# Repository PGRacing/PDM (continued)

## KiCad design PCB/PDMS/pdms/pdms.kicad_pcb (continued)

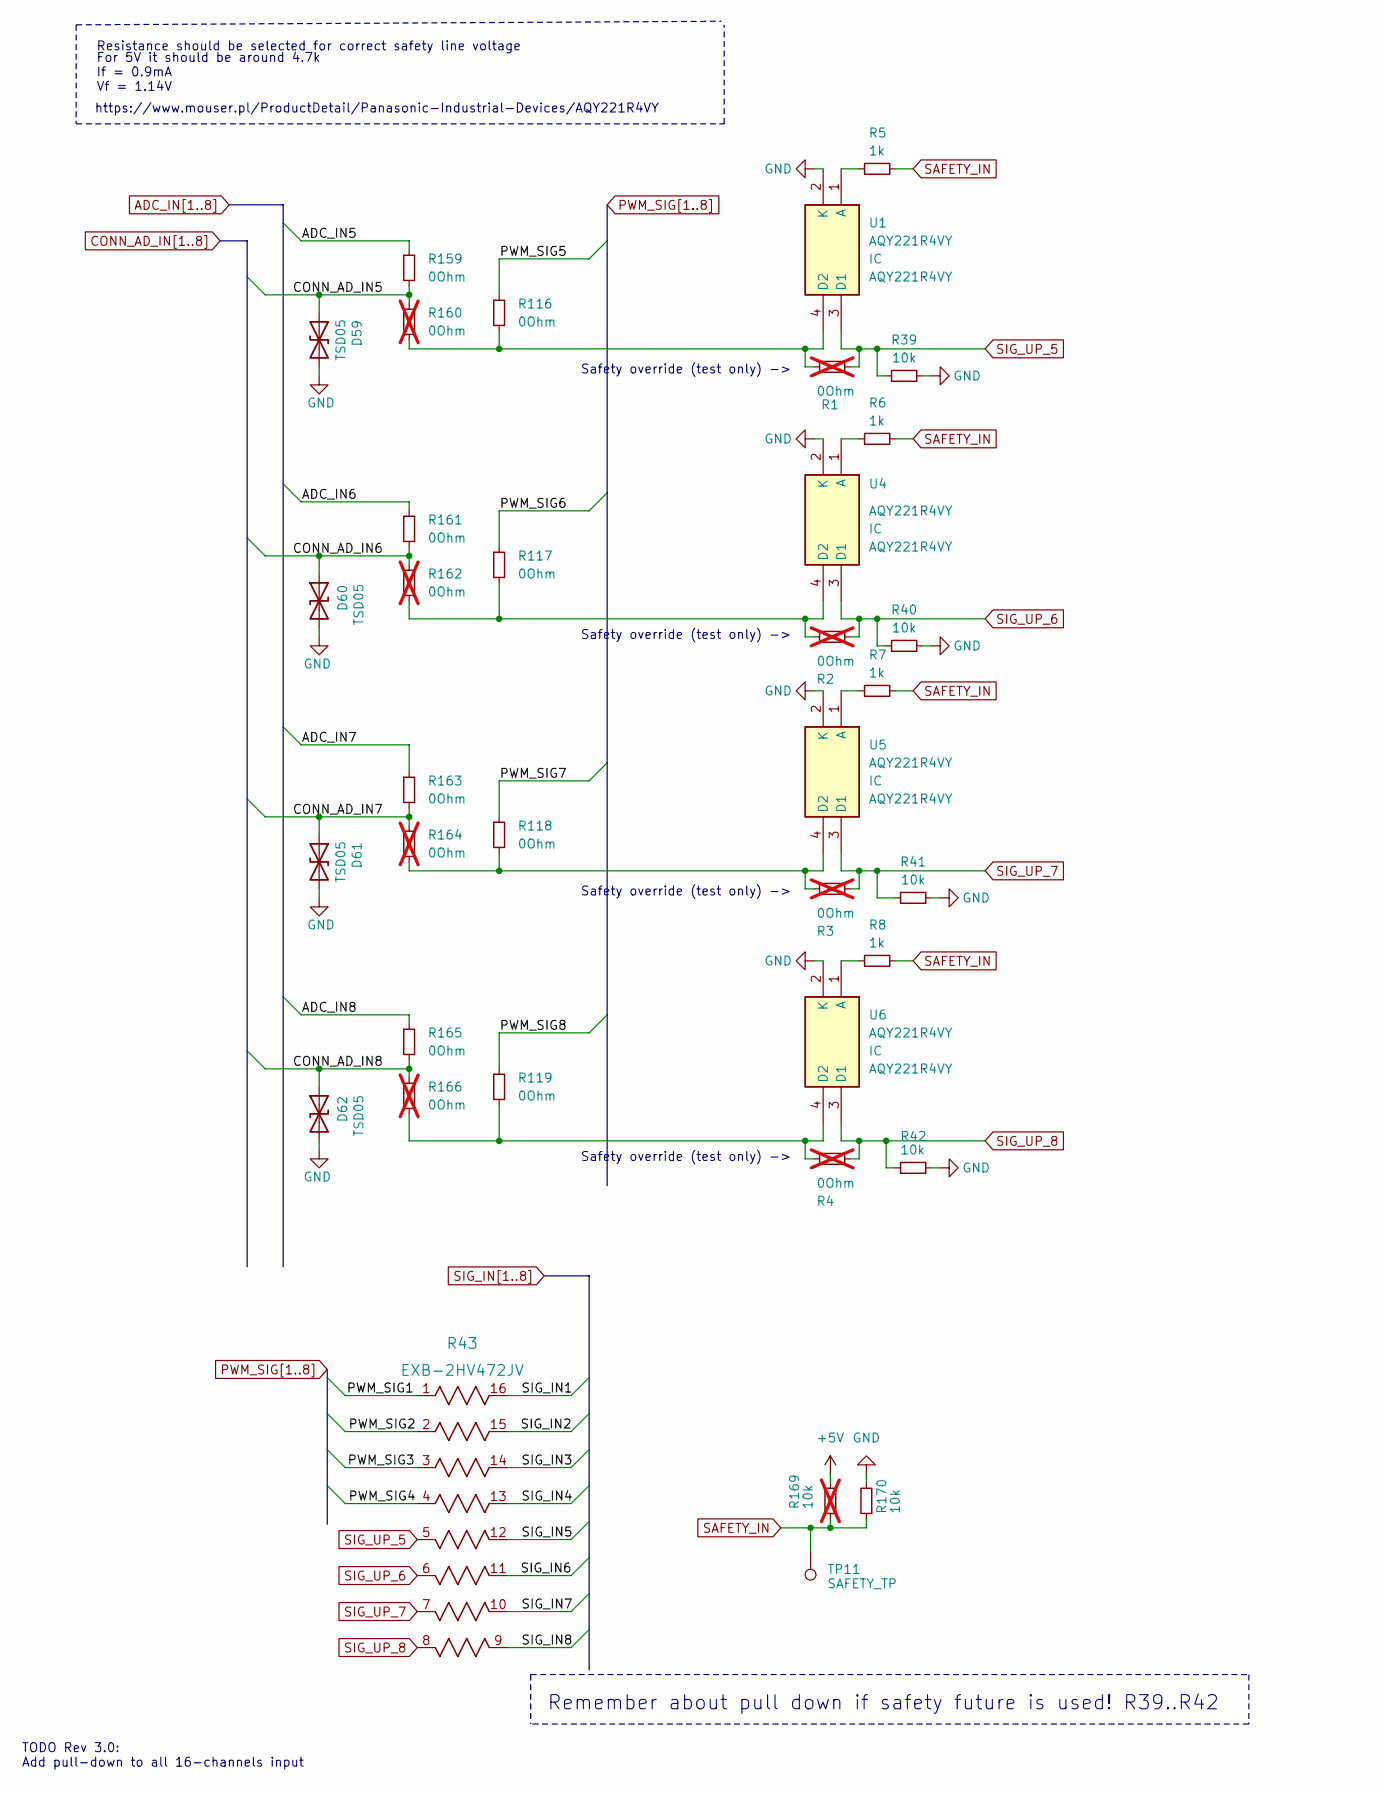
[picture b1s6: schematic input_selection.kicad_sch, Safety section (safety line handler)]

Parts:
D59, D60, D61, D62: TSD05; D_SOD-323
R1, R2, R3, R4, R160, R162, R164, R166: 0Ohm; R_0402_1005Metric; not fitted
R5, R6, R7, R8: 1k; R_0402_1005Metric
R39, R40, R41, R42, R170: 10k; R_0402_1005Metric
R43: EXB-2HV472JV; RES_EXB2HV
R116, R117, R118, R119, R159, R161, R163, R165: 0Ohm; R_0402_1005Metric
R169: 10k; R_0402_1005Metric; not fitted
TP11: SAFETY_TP; TestPoint_Pad_D2.0mm
U1, U4, U5, U6: AQY221R4VY; SOTFL127P485X190-4N; Manufacturer_Part_Number AQY221R4VY; Mouser Part Number 769-AQY221R4VY

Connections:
+5V: R169.2; also elsewhere on the board
ADC_IN5: R159.1; also elsewhere on the board
ADC_IN6: R161.1; also elsewhere on the board
ADC_IN7: R163.1; also elsewhere on the board
ADC_IN8: R165.1; also elsewhere on the board
CONN_AD_IN5: D59.1 (A1), R159.2, R160.1; also elsewhere on the board
CONN_AD_IN6: D60.1 (A1), R161.2, R162.1; also elsewhere on the board
CONN_AD_IN7: D61.1 (A1), R163.2, R164.1; also elsewhere on the board
CONN_AD_IN8: D62.1 (A1), R165.2, R166.1; also elsewhere on the board
unnamed: R5.1, U1.1 (A)
unnamed: R6.1, U4.1 (A)
unnamed: R7.1, U5.1 (A)
unnamed: R3.2, R118.2, R164.2, U5.4 (D2)
unnamed: R8.1, U6.1 (A)
unnamed: R4.2, R119.2, R166.2, U6.4 (D2)
PWM_SIG1: R43.1; also elsewhere on the board
PWM_SIG2: R43.2; also elsewhere on the board
PWM_SIG3: R43.3; also elsewhere on the board
PWM_SIG4: R43.4; also elsewhere on the board
PWM_SIG5: R116.1; also elsewhere on the board
PWM_SIG6: R117.1; also elsewhere on the board
PWM_SIG7: R118.1; also elsewhere on the board
PWM_SIG8: R119.1; also elsewhere on the board
SAFETY_IN: R5.2, R6.2, R7.2, R8.2, R169.1, R170.1, TP11.1; also elsewhere on the board
SIG_IN1: R43.16; also elsewhere on the board
SIG_IN2: R43.15; also elsewhere on the board
SIG_IN3: R43.14; also elsewhere on the board
SIG_IN4: R43.13; also elsewhere on the board
SIG_IN5: R43.12; also elsewhere on the board
SIG_IN6: R43.11; also elsewhere on the board
SIG_IN7: R43.10; also elsewhere on the board
SIG_IN8: R43.9; also elsewhere on the board
SIG_UP_7: R3.1, R41.1, R43.7, U5.3 (D1)
SIG_UP_8: R4.1, R42.1, R43.8, U6.3 (D1)

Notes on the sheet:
For 5V it should be around 4.7k If = 0.9mA Vf = 1.14V
Remember about pull down if safety future is used! R39..R42
Safety override (test only) ->
Resistance should be selected for correct safety line voltage
https://www.mouser.pl/ProductDetail/Panasonic-Industrial-Devices/AQY221R4VY
TODO Rev 3.0: Add pull-down to all 16-channels input

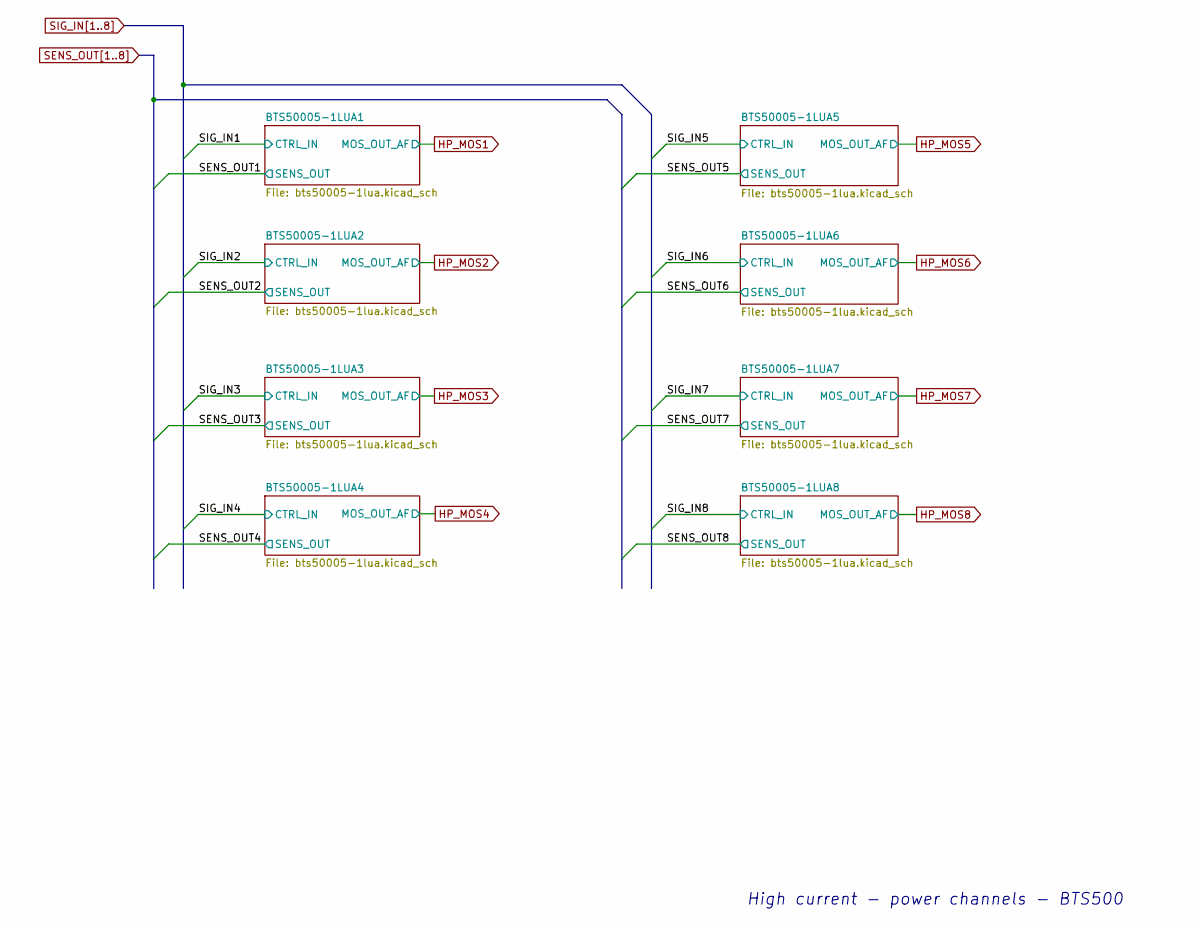
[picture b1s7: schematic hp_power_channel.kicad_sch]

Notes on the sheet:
High current - power channels - BTS500

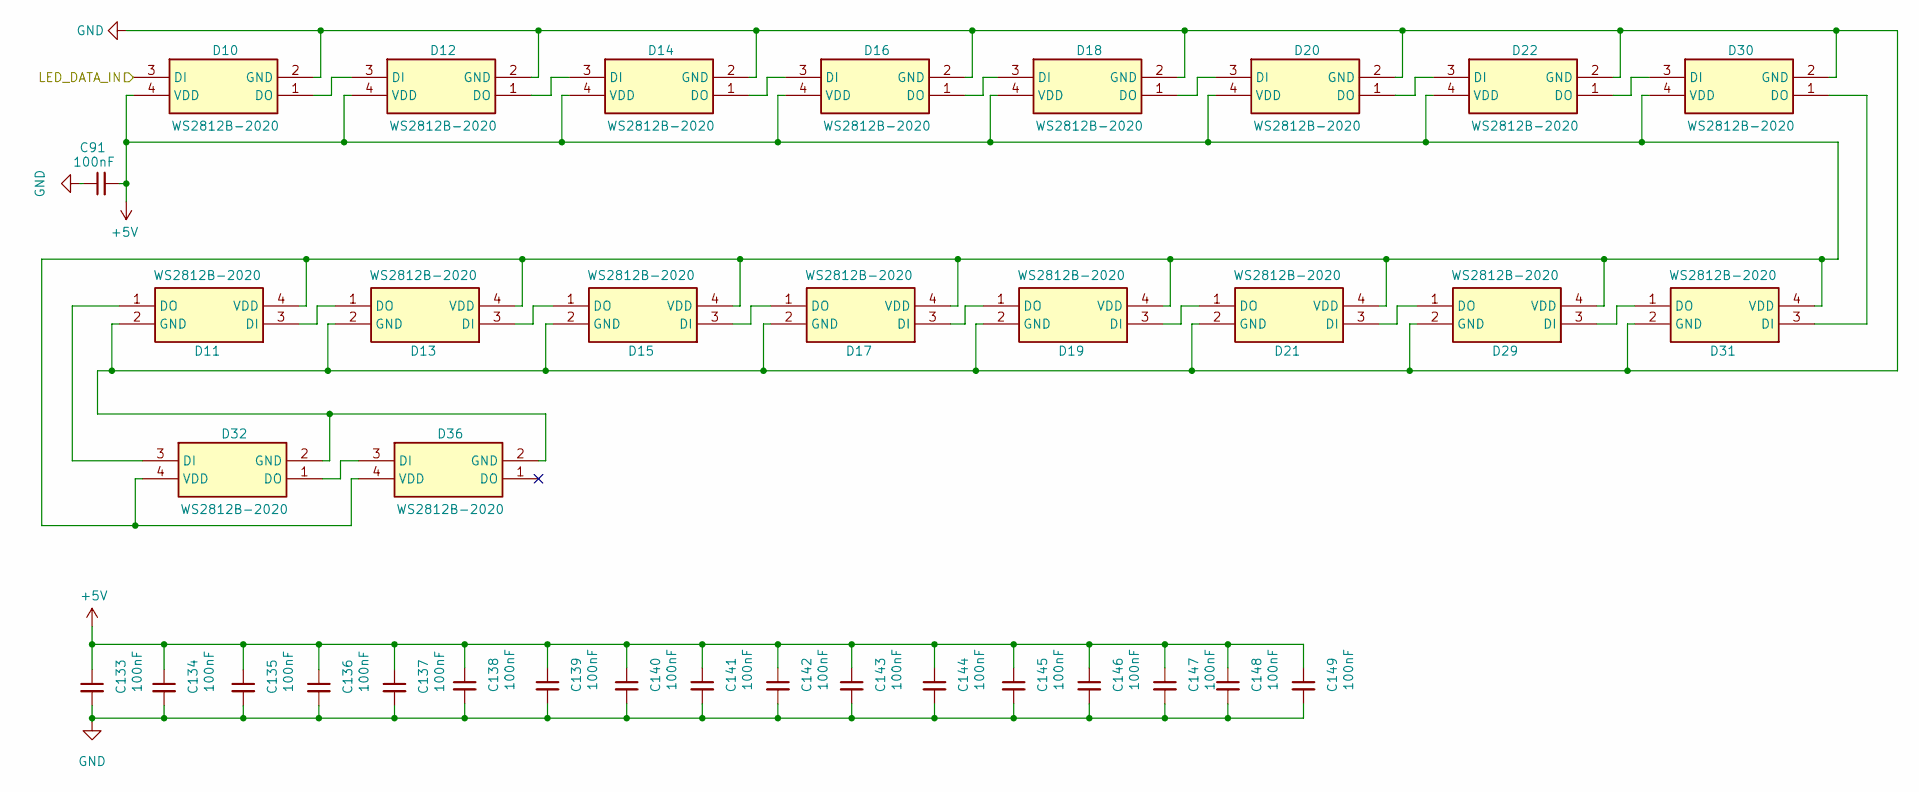
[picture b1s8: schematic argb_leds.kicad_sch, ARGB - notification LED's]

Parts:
C91, C133, C134, C135, C136, C137, C138, C139, C140, C141, C142, C143, C144, C145, C146, C147, C148, C149: 100nF; R_0402_1005Metric
D10, D11, D12, D13, D14, D15, D16, D17, D18, D19, D20, D21, D22, D29, D30, D31, D32, D36: WS2812B-2020; WS2812B2020; Manufacturer_Part_Number WS2812B-2020

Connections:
+5V: C91.2, C133.1, C134.1, C135.1, C136.1, C137.1, C138.1, C139.1, C140.1, C141.1, C142.1, C143.1, C144.1, C145.1, C146.1, C147.1, C148.1, C149.1, D10.4 (VDD), D11.4 (VDD), D12.4 (VDD), D13.4 (VDD), D14.4 (VDD), D15.4 (VDD), D16.4 (VDD), D17.4 (VDD), D18.4 (VDD), D19.4 (VDD), D20.4 (VDD), D21.4 (VDD), D22.4 (VDD), D29.4 (VDD), D30.4 (VDD), D31.4 (VDD), D32.4 (VDD), D36.4 (VDD); also elsewhere on the board
/ARGB_LEDS/LED_DATA_IN: D10.3 (DI); also elsewhere on the board
unnamed: D10.1 (DO), D12.3 (DI)
unnamed: D11.3 (DI), D13.1 (DO)
unnamed: D11.1 (DO), D32.3 (DI)
unnamed: D12.1 (DO), D14.3 (DI)
unnamed: D13.3 (DI), D15.1 (DO)
unnamed: D14.1 (DO), D16.3 (DI)
unnamed: D15.3 (DI), D17.1 (DO)
unnamed: D16.1 (DO), D18.3 (DI)
unnamed: D17.3 (DI), D19.1 (DO)
unnamed: D18.1 (DO), D20.3 (DI)
unnamed: D19.3 (DI), D21.1 (DO)
unnamed: D20.1 (DO), D22.3 (DI)
unnamed: D21.3 (DI), D29.1 (DO)
unnamed: D22.1 (DO), D30.3 (DI)
unnamed: D29.3 (DI), D31.1 (DO)
unnamed: D30.1 (DO), D31.3 (DI)
unnamed: D32.1 (DO), D36.3 (DI)

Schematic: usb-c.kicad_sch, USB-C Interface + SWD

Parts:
J6: 2305018-2; TE_2305018-2; not fitted
R173, R175: 1k5; R_0402_1005Metric; not fitted
R174, R176: 22; R_0402_1005Metric; not fitted
R177, R178: 5.1k; R_0402_1005Metric; not fitted
R179, R180: 0; R_0402_1005Metric; not fitted
U12: USBLC6-2SC6; SOT-23-6; not fitted

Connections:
+5V: U12.5 (VBUS); also elsewhere on the board
/USB-C/USB_D+: U12.4 (I/O2); also elsewhere on the board
/USB-C/USB_D-: U12.6 (I/O1); also elsewhere on the board
unnamed: J6.A5 (CC1), R177.1
unnamed: J6.B5 (CC2), R178.1
unnamed: R174.1, U12.1 (I/O1)
unnamed: R176.2, U12.3 (I/O2)
SWCLK: R180.1; also elsewhere on the board
SWDIO: R179.1; also elsewhere on the board
USBC_SWCLK: J6.A10 (RX2_N), J6.B10 (RX1_N), R180.2
USBC_SWDIO: J6.A11 (RX2_P), J6.B11 (RX1_P), R179.2
USB_CONN_D+: J6.A6 (DA_P), J6.B6 (DB_P), R175.1, R176.1
USB_CONN_D-: J6.A7 (DA_N), J6.B7 (DB_N), R173.1, R174.2

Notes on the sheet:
USB-C Legacy mode + Optional STLINK
USB-C Interface + SWD

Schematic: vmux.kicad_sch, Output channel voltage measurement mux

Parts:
C2, C112: 100nF; C_0402_1005Metric
C107: 47nF; C_0402_1005Metric
C1901, C1902, C1903, C1904, C1905, C1906, C1907, C1908: 4.7uF; C_0402_1005Metric
D38: BAT54SW; SOT-323_SC-70
D67: SZMM5Z3V9; D_SOD-523
IC2: 74HC4067PW-Q100J; SOP65P640X110-24N; Manufacturer_Part_Number 74HC4067PW-Q100J; Mouser Part Number 771-74HC4067PW-Q100J
R10, R13, R14, R17, R18, R33, R34, R37, R45, R48, R49, R52, R53, R88, R89, R92: 2.3k; R_0402_1005Metric
R11, R12, R15, R16, R19, R32, R35, R36, R46, R47, R50, R51, R65, R87, R90, R91: 10k; R_0402_1005Metric
R122: 1k; R_0402_1005Metric
U13: MCP6001-OT; SOT-23-5

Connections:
/VMUX/HP_MOS_DIV1: C1908.2, IC2.9 (Y0), R35.1, R37.2
/VMUX/HP_MOS_DIV2: C1907.2, IC2.8 (Y1), R19.1, R33.2
/VMUX/HP_MOS_DIV3: C1906.2, IC2.7 (Y2), R15.1, R17.2
/VMUX/HP_MOS_DIV4: C1905.2, IC2.6 (Y3), R11.1, R13.2
/VMUX/HP_MOS_DIV5: C1901.2, IC2.5 (Y4), R10.2, R12.1
/VMUX/HP_MOS_DIV6: C1902.2, IC2.4 (Y5), R14.2, R16.1
/VMUX/HP_MOS_DIV7: C1903.2, IC2.3 (Y6), R18.2, R32.1
/VMUX/HP_MOS_DIV8: C1904.2, IC2.2 (Y7), R34.2, R36.1
/VMUX/LP_MOS_DIV1: IC2.23 (Y8), R45.2, R47.1
/VMUX/LP_MOS_DIV2: IC2.22 (Y9), R49.2, R51.1
/VMUX/LP_MOS_DIV3: IC2.21 (Y10), R53.2, R87.1
/VMUX/LP_MOS_DIV4: IC2.20 (Y11), R89.2, R91.1
/VMUX/LP_MOS_DIV5: IC2.19 (Y12), R90.1, R92.2
/VMUX/LP_MOS_DIV6: IC2.18 (Y13), R65.1, R88.2
/VMUX/LP_MOS_DIV7: IC2.17 (Y14), R50.1, R52.2
/VMUX/LP_MOS_DIV8: IC2.16 (Y15), R46.1, R48.2
/VMUX/VMUX_SEL1: IC2.10 (S0); also elsewhere on the board
/VMUX/VMUX_SEL2: IC2.11 (S1); also elsewhere on the board
/VMUX/VMUX_SEL3: IC2.14 (S2); also elsewhere on the board
/VMUX/VMUX_SEL4: IC2.13 (S3); also elsewhere on the board
HP_MOS1: R15.2; also elsewhere on the board
HP_MOS2: R12.2; also elsewhere on the board
HP_MOS3: R11.2; also elsewhere on the board
HP_MOS4: R16.2; also elsewhere on the board
HP_MOS5: R32.2; also elsewhere on the board
HP_MOS6: R36.2; also elsewhere on the board
HP_MOS7: R35.2; also elsewhere on the board
HP_MOS8: R19.2; also elsewhere on the board
LP_MOS1: R47.2; also elsewhere on the board
LP_MOS2: R51.2; also elsewhere on the board
LP_MOS3: R87.2; also elsewhere on the board
LP_MOS4: R91.2; also elsewhere on the board
LP_MOS5: R90.2; also elsewhere on the board
LP_MOS6: R65.2; also elsewhere on the board
LP_MOS7: R50.2; also elsewhere on the board
LP_MOS8: R46.2; also elsewhere on the board
unnamed: D38.3, D67.1 (K), IC2.1 (Z), U13.3 (+)

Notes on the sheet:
In case you would ever consider to limit number of voltage dividers, the HC4067 operating range is up to 11V MAX!, It is really difficult to find 16 channel mux with extended input voltage range
IMPORTANT: On top of 2.3k resistors, there is 4.7uF capacitor soldered, to average out PWM from output voltage
In case of an reverse polarity situation, there might be an issue that +3.3V line is not powered, but HP_MOS out is, in such situation current should be limited by resistor
SZMM5Z3V9T1G
This values were verified! 2.32k and 10k is ok 2.32kOhm instead of 2.3k is used due to availabillity
(3.3kHz cut-off)

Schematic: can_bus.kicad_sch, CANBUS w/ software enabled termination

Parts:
C64, C65, C87: 100nF; C_0402_1005Metric
D27, D28: PESD2CANFD24L-UX; SOT65P210X110-3N; Manufacturer_Part_Number PESD2CANFD24L-UX; Mouser Part Number 771-PESD2CANFD24L-UX
IC17: TS5A21366DCUR; SOP50P310X90-8N; Manufacturer_Part_Number TS5A21366DCUR; Mouser Part Number 595-TS5A21366DCUR
R58, R59: 120; R_0402_1005Metric
U2, U3: MCP2561-E-SN; SOIC-8_3.9x4.9mm_P1.27mm

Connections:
+5V: C64.1, C65.1, C87.2, IC17.8 (V+), U2.3 (VDD), U3.3 (VDD); also elsewhere on the board
/CAN_BUS/CAN1_RX: U2.4 (RXD); also elsewhere on the board
/CAN_BUS/CAN1_TX: U2.1 (TXD); also elsewhere on the board
/CAN_BUS/CAN2_RX: U3.4 (RXD); also elsewhere on the board
/CAN_BUS/CAN2_TX: U3.1 (TXD); also elsewhere on the board
/CAN_BUS/CAN_TERMINATOR_1: IC17.7 (IN1); also elsewhere on the board
/CAN_BUS/CAN_TERMINATOR_2: IC17.3 (IN2); also elsewhere on the board
CAN1_H: D27.1 (K1), IC17.1 (NO1), U2.7 (CANH); also elsewhere on the board
CAN1_L: D27.2 (K2), R58.1, U2.6 (CANL); also elsewhere on the board
CAN2_H: D28.1 (K1), R59.1, U3.7 (CANH); also elsewhere on the board
CAN2_L: D28.2 (K2), IC17.6 (COM2), U3.6 (CANL); also elsewhere on the board
unnamed: IC17.2 (COM1), R58.2
unnamed: IC17.5 (NO2), R59.2

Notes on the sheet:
For commercial application this should be changed to solution that can persist at least 250mA continous short current
CAN1
Software termination for CAN1 & CAN2
CAN2

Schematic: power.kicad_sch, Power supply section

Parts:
C1: 4.7uF; C_0805_2012Metric
C3, C5, C90: 1uF; C_0805_2012Metric
C4, C92: 4.7uF; C_0603_1608Metric
C6, C7, C8, C9, C10, C11, C12, C13: 10uF; C_1206_3216Metric
C21: 100pF/50V; C_0402_1005Metric
C22: 100nF/50V; C_0402_1005Metric
C54: 1uF; C_0805_2012Metric; not fitted
C55: 4.7uF; C_0603_1608Metric; not fitted
C88: 1000uF; CP_Radial_D12.5mm_P5.00mm
D51, D52: SMC_TVS_28V; D_SMC
D53: 1N4448WS; D_SOD-323
D54: 1N4448WS; D_SOD-323; not fitted
F1: 2A; Fuse_1206_3216Metric
F2, F19, F23: 1A; Fuse_0805_2012Metric
F3: 3A; Fuse_0805_2012Metric
F18: 500mA; Fuse_0805_2012Metric; not fitted
FB1: 742792063; L_0805_2012Metric
IC1: BD50FD0WHFP-TR; BD50FD0WHFPTR; Manufacturer_Part_Number BD50FD0WHFP-TR; Mouser Part Number 755-BD50FD0WHFP-TR
IC3: LDO40LPU33RY; SON95P300X300X90-7N-D; Manufacturer_Part_Number LDO40LPU33RY; Mouser Part Number 511-LDO40LPU33RY
IC10: LDO40LPU50RY; SON95P300X300X90-7N-D; Manufacturer_Part_Number LDO40LPU50RY; Mouser Part Number 511-LDO40LPU50RY; not fitted
IC14: LDO40LPU50RY; SON95P300X300X90-7N-D; Manufacturer_Part_Number LDO40LPU50RY; Mouser Part Number 511-LDO40LPU50RY
L3: 10uH / 1A; L_6.3x6.3_H3
Q1, Q11: Si2319CDS; SOT-23
TP1: 3.3V PG; TestPoint_Pad_D1.0mm
TP10: 5V; TestPoint_Pad_D2.0mm
TP13: 3.3V; TestPoint_Pad_D2.0mm

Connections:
+3.3VP: F2.1; also elsewhere on the board
+5V: F18.1, F23.1, TP10.1; also elsewhere on the board
+5VL: F19.1; also elsewhere on the board
+12V: C88.1, D51.2 (A2), D52.2 (A2), F1.1, Q11.3 (D); also elsewhere on the board
+12VA: F3.1; also elsewhere on the board
/POWER1/PREFUSE_5VL: C92.1, F19.2, IC14.4 (VOUT), IC14.5 (VSENSE)
/POWER1/VOUT: C55.1, D54.2 (A), F18.2, IC10.2 (EN), IC10.3 (VIN)
unnamed: C21.1, C22.1, FB1.1, L3.2
unnamed: F1.2, Q1.3 (D)

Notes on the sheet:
This should be changed to CLC - Pi filter Change this to electrolytic cap
X7R capacitors close to pins
LDO 3.3V - EXTERNAL
B82462G4103M
Min. 25V 600-2000uF
This TVS should be uni-directional
1N4448WS should be placed here
BUCK 3.3V - INTERNAL
LDO 5V - INTERNAL
LDO 5V - INTERNAL (BIGGER FOOTPRINT)
PROTECTED BATT SUPPLY - EXTERNAL
Minimal fuse rating for 0805 is 250mA
REVERSE POLARITY + SUPPLY FILTER
This needs to be changed to Si2319CDS due to too low Vgss
INPUT FILTER & PROTECTION
LDO 5V - EXTERNAL
This needs to be changed to Si2319CDS due to too low Vgss ADD FUSE!

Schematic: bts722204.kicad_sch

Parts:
C14, C15, C16, C17: 10nF; C_0603_1608Metric
C18: 220pF; C_0402_1005Metric
C19: 470nF; C_0805_2012Metric
C20: 100nF; C_0805_2012Metric
D39: BAT54SW; SOT-323_SC-70
D49: SZMM5Z3V9; D_SOD-523
IC7: BTS722204ESAXUMA1; SOP65P600X115-25N; Manufacturer_Part_Number BTS722204ESAXUMA1; Mouser Part Number 726-BTS722204ESAXUMA
R20, R21, R22, R23, R31, R44: 1.2k; R_0402_1005Metric
R24, R25, R26, R27, R30, R114: 4.7k; R_0402_1005Metric
R28: 47; R_0805_2012Metric
R29: 470; R_0402_1005Metric

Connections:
+12V: C20.2, IC7.25 (VS); also elsewhere on the board
/LP_POWER_CHANNEL/BTS722204-1/IS: IC7.12 (IS), R31.1, R114.2
/LP_POWER_CHANNEL/BTS722204-1/LHI: IC7.7 (LHI), R44.1
/LP_POWER_CHANNEL/BTS722204-1/OUT0: C14.1, IC7.21 (OUT0_1), IC7.22 (OUT0_2), IC7.23 (OUT0_3), IC7.24 (OUT0_4); also elsewhere on the board
/LP_POWER_CHANNEL/BTS722204-1/OUT1: C15.1, IC7.19 (OUT1_1), IC7.20 (OUT1_2); also elsewhere on the board
/LP_POWER_CHANNEL/BTS722204-1/OUT2: C16.1, IC7.17 (OUT2_1), IC7.18 (OUT2_2); also elsewhere on the board
/LP_POWER_CHANNEL/BTS722204-1/OUT3: C17.1, IC7.13 (OUT3_1), IC7.14 (OUT3_2), IC7.15 (OUT3_3), IC7.16 (OUT3_4); also elsewhere on the board
/LP_POWER_CHANNEL/BTS722204-1/SI: IC7.4 (SI), R21.1
/LP_POWER_CHANNEL/BTS722204-1/SO: IC7.3 (SO), R20.1
/LP_POWER_CHANNEL/BTS722204-1/VDD_IO: C19.2, IC7.2 (VDD), R29.1
LP_CSN1: R23.2; also elsewhere on the board
LP_SIG_IN1: R24.1; also elsewhere on the board
LP_SIG_IN2: R25.1; also elsewhere on the board
LP_SIG_IN3: R26.1; also elsewhere on the board
LP_SIG_IN4: R27.1; also elsewhere on the board
unnamed: D39.3, D49.1 (K), R30.1, R114.1
unnamed: IC7.6 (CSN), R23.1
unnamed: C19.1, IC7.1 (GND_1), R28.1
unnamed: IC7.8 (IN0), R24.2
unnamed: IC7.9 (IN1), R25.2
unnamed: IC7.10 (IN2), R26.2
unnamed: IC7.11 (IN3), R27.2
unnamed: IC7.5 (SCLK), R22.1
SENS_OUT_LP1: C18.1, R30.2; also elsewhere on the board
SPI2_MISO: R20.2; also elsewhere on the board
SPI2_MOSI: R21.2; also elsewhere on the board
SPI2_SCK: R22.2; also elsewhere on the board

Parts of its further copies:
C67: 220pF; C_0402_1005Metric
C68: 470nF; C_0805_2012Metric
C69: 100nF; C_0805_2012Metric
C70, C71, C72, C73: 10nF; C_0603_1608Metric
D40: BAT54SW; SOT-323_SC-70
D50: SZMM5Z3V9; D_SOD-523
IC16: BTS722204ESAXUMA1; SOP65P600X115-25N; Manufacturer_Part_Number BTS722204ESAXUMA1; Mouser Part Number 726-BTS722204ESAXUMA
R93, R97, R98, R99, R100, R105: 1.2k; R_0402_1005Metric
R94: 47; R_0805_2012Metric
R95: 470; R_0402_1005Metric
R96, R101, R102, R103, R104, R115: 4.7k; R_0402_1005Metric

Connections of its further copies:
+12V: C69.2, IC16.25 (VS); also elsewhere on the board
/LP_POWER_CHANNEL/BTS722204-2/IS: IC16.12 (IS), R105.1, R115.2
/LP_POWER_CHANNEL/BTS722204-2/LHI: IC16.7 (LHI), R93.1
/LP_POWER_CHANNEL/BTS722204-2/OUT0: C70.1, IC16.21 (OUT0_1), IC16.22 (OUT0_2), IC16.23 (OUT0_3), IC16.24 (OUT0_4); also elsewhere on the board
/LP_POWER_CHANNEL/BTS722204-2/OUT1: C71.1, IC16.19 (OUT1_1), IC16.20 (OUT1_2); also elsewhere on the board
/LP_POWER_CHANNEL/BTS722204-2/OUT2: C72.1, IC16.17 (OUT2_1), IC16.18 (OUT2_2); also elsewhere on the board
/LP_POWER_CHANNEL/BTS722204-2/OUT3: C73.1, IC16.13 (OUT3_1), IC16.14 (OUT3_2), IC16.15 (OUT3_3), IC16.16 (OUT3_4); also elsewhere on the board
/LP_POWER_CHANNEL/BTS722204-2/SI: IC16.4 (SI), R98.1
/LP_POWER_CHANNEL/BTS722204-2/SO: IC16.3 (SO), R97.1
/LP_POWER_CHANNEL/BTS722204-2/VDD_IO: C68.2, IC16.2 (VDD), R95.1
LP_CSN2: R100.2; also elsewhere on the board
LP_SIG_IN5: R101.1; also elsewhere on the board
LP_SIG_IN6: R102.1; also elsewhere on the board
LP_SIG_IN7: R103.1; also elsewhere on the board
LP_SIG_IN8: R104.1; also elsewhere on the board
unnamed: D40.3, D50.1 (K), R96.1, R115.1
unnamed: IC16.6 (CSN), R100.1
unnamed: C68.1, IC16.1 (GND_1), R94.1
unnamed: IC16.8 (IN0), R101.2
unnamed: IC16.9 (IN1), R102.2
unnamed: IC16.10 (IN2), R103.2
unnamed: IC16.11 (IN3), R104.2
unnamed: IC16.5 (SCLK), R99.1
SENS_OUT_LP2: C67.1, R96.2; also elsewhere on the board
SPI2_MISO: R97.2; also elsewhere on the board
SPI2_MOSI: R98.2; also elsewhere on the board
SPI2_SCK: R99.2; also elsewhere on the board

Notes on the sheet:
Ris_prot -> value should be checked properly
BTS72220 - 4 channel high side switch

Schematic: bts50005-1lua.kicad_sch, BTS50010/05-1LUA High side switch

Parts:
C114: 100nF; C_0402_1005Metric
C115: 1nF; C_0402_1005Metric
C116: 10nF; C_0402_1005Metric
C117: 100nF; C_0805_2012Metric
D6: BAT54SW; SOT-323_SC-70
D45: SZMM5Z3V9; D_SOD-523
F8: 40A; Fuse_1206_3216Metric
Q7: BTS500101LUAAUMA1; Manufacturer_Part_Number BTS500101LUAAUMA1; Mouser Part Number 726-BTS500101LUAAUMA
R110, R199: 4.7k; R_0402_1005Metric
R201: 1k; R_0402_1005Metric
TP6: AFUSE; TestPoint_Pad_D2.0mm

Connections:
+12V: C115.1, C117.1, Q7.4 (DEN), Q7.9 (VS); also elsewhere on the board
/HP_POWER_CHANNEL/BTS50005-1LUA5/MOS_OUT: C116.2, F8.1, Q7.5 (OUT)
HP_MOS5: F8.2, TP6.1; also elsewhere on the board
unnamed: D6.3, D45.1 (K), R110.1, R199.2
unnamed: C115.2, Q7.2 (IS), R110.2, R201.2
SENS_OUT5: C114.2, R199.1; also elsewhere on the board
SIG_IN5: Q7.3 (IN); also elsewhere on the board

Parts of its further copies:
C93, C98, C103, C108, C119, C124, C129: 100nF; C_0402_1005Metric
C94, C100, C105, C110, C121, C126, C131: 10nF; C_0402_1005Metric
C95, C101, C106, C111, C122, C127, C132: 100nF; C_0805_2012Metric
C99, C104, C109, C113, C120, C125, C130: 1nF; C_0402_1005Metric
D1, D2, D3, D5, D7, D8, D9: BAT54SW; SOT-323_SC-70
D41, D42, D43, D44, D46, D47, D48: SZMM5Z3V9; D_SOD-523
F4, F5, F6, F7, F9, F21, F22: 40A; Fuse_1206_3216Metric
Q3, Q4, Q5, Q6, Q8, Q9, Q10: BTS500101LUAAUMA1; Manufacturer_Part_Number BTS500101LUAAUMA1; Mouser Part Number 726-BTS500101LUAAUMA
R9, R38, R106, R107, R111, R112, R113, R183, R188, R193, R198, R204, R209, R214: 4.7k; R_0402_1005Metric
R67, R185, R190, R195, R206, R211, R216: 1k; R_0402_1005Metric
TP2, TP3, TP4, TP5, TP7, TP8, TP9: AFUSE; TestPoint_Pad_D2.0mm

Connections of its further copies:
+12V: C95.1, C99.1, C101.1, C104.1, C106.1, C109.1, C111.1, C113.1, C120.1, C122.1, C125.1, C127.1, C130.1, C132.1, Q3.4 (DEN), Q3.9 (VS), Q4.4 (DEN), Q4.9 (VS), Q5.4 (DEN), Q5.9 (VS), Q6.4 (DEN), Q6.9 (VS), Q8.4 (DEN), Q8.9 (VS), Q9.4 (DEN), Q9.9 (VS), Q10.4 (DEN), Q10.9 (VS); also elsewhere on the board
/HP_POWER_CHANNEL/BTS50005-1LUA1/MOS_OUT: C94.2, F7.1, Q3.5 (OUT)
/HP_POWER_CHANNEL/BTS50005-1LUA2/MOS_OUT: C100.2, F4.1, Q4.5 (OUT)
/HP_POWER_CHANNEL/BTS50005-1LUA3/MOS_OUT: C105.2, F5.1, Q5.5 (OUT)
/HP_POWER_CHANNEL/BTS50005-1LUA4/MOS_OUT: C110.2, F6.1, Q6.5 (OUT)
/HP_POWER_CHANNEL/BTS50005-1LUA6/MOS_OUT: C121.2, F9.1, Q8.5 (OUT)
/HP_POWER_CHANNEL/BTS50005-1LUA7/MOS_OUT: C126.2, F21.1, Q9.5 (OUT)
/HP_POWER_CHANNEL/BTS50005-1LUA8/MOS_OUT: C131.2, F22.1, Q10.5 (OUT)
HP_MOS1: F7.2, TP5.1; also elsewhere on the board
HP_MOS2: F4.2, TP2.1; also elsewhere on the board
HP_MOS3: F5.2, TP3.1; also elsewhere on the board
HP_MOS4: F6.2, TP4.1; also elsewhere on the board
HP_MOS6: F9.2, TP7.1; also elsewhere on the board
HP_MOS7: F21.2, TP8.1; also elsewhere on the board
HP_MOS8: F22.2, TP9.1; also elsewhere on the board
unnamed: D1.3, D41.1 (K), R9.1, R183.2
unnamed: D2.3, D42.1 (K), R38.1, R188.2
unnamed: D3.3, D43.1 (K), R106.1, R193.2
unnamed: D5.3, D44.1 (K), R107.1, R198.2
unnamed: D7.3, D46.1 (K), R111.1, R204.2
unnamed: D8.3, D47.1 (K), R112.1, R209.2
unnamed: D9.3, D48.1 (K), R113.1, R214.2
unnamed: C113.2, Q3.2 (IS), R67.2, R107.2
unnamed: C99.2, Q4.2 (IS), R9.2, R185.2
unnamed: C104.2, Q5.2 (IS), R38.2, R190.2
unnamed: C109.2, Q6.2 (IS), R106.2, R195.2
unnamed: C120.2, Q8.2 (IS), R111.2, R206.2
unnamed: C125.2, Q9.2 (IS), R112.2, R211.2
unnamed: C130.2, Q10.2 (IS), R113.2, R216.2
SENS_OUT1: C93.2, R198.1; also elsewhere on the board
SENS_OUT2: C98.2, R183.1; also elsewhere on the board
SENS_OUT3: C103.2, R188.1; also elsewhere on the board
SENS_OUT4: C108.2, R193.1; also elsewhere on the board
SENS_OUT6: C119.2, R204.1; also elsewhere on the board
SENS_OUT7: C124.2, R209.1; also elsewhere on the board
SENS_OUT8: C129.2, R214.1; also elsewhere on the board
SIG_IN1: Q3.3 (IN); also elsewhere on the board
SIG_IN2: Q4.3 (IN); also elsewhere on the board
SIG_IN3: Q5.3 (IN); also elsewhere on the board
SIG_IN4: Q6.3 (IN); also elsewhere on the board
SIG_IN6: Q8.3 (IN); also elsewhere on the board
SIG_IN7: Q9.3 (IN); also elsewhere on the board
SIG_IN8: Q10.3 (IN); also elsewhere on the board

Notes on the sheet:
IMPORTANT: - DEN should be pulsed with IN. - DEN should be connected to IN via some resistor. - Right now when channel is in PWM mode (duty off part) and DEN enabled, it puts hard fault on output, due to open-circuit detection (till Vout discharges till < Typ. 3V - Link to forum
Check if RC filter values are correct: Sense signal filtering A time constant (RADC * CSENSE ) longer than 1 μs is recommended
Conditional Ris > 2.5k
For sake of accuracy of current sense BTS50010 should be used
SZMM5Z3V9T1G
<- Currently 8k2 0.1%
Ris_prot -> value should be checked properly
Sense resistor accuracy important!

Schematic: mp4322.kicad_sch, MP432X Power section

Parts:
C1: 1nF; C_0402_1005Metric
C2: 10nF; C_0402_1005Metric
C3, C4: 2.2uF; C_0805_2012Metric
C5: 22uF; CP_Elec_6.3x9.9
C23, C24: 4.7uF; C_1206_3216Metric
C25, C26: 0.1uF; C_0805_2012Metric
C27: 1uF; C_0402_1005Metric
C28: 47nF; C_0402_1005Metric
C29: 10pF; C_0402_1005Metric
C30, C31: 22uF; C_1206_3216Metric
C61, C62: 10uF; C_1206_3216Metric; not fitted
C63: 2.2uF; C_1206_3216Metric; not fitted
F24: 2A; Fuse_0805_2012Metric
L1: 742792063; L_0805_2012Metric
L2: XEL4020-102MEB; L_Coilcraft_XxL4020
L4: 2.2uH; L_Vishay_IHLP-1616
R1: 0R0; R_0402_1005Metric
R2: NA; R_0402_1005Metric; not fitted
R120: 15k; R_0402_1005Metric
R121, R122, R124: 100k; R_0402_1005Metric
R123: 31.6k; R_0402_1005Metric
U7: MP4322GDE-P; QFN-12_MP4322_MNP

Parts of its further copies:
C56: 47nF; C_0402_1005Metric
C57: 10pF; C_0402_1005Metric
C58, C59: 22uF; C_1206_3216Metric
C60: 1uF; C_0402_1005Metric
F20: 2A; Fuse_0805_2012Metric
L5: 2.2uH; L_Vishay_IHLP-1616
R60: 0R0; R_0402_1005Metric
R61, R63, R64: 100k; R_0402_1005Metric
R62: 15k; R_0402_1005Metric

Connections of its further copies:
unnamed: C56.1, R60.1

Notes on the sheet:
(1206)
12V FILTERING
If electrolytic cap won't fit
When creating layout always follow guidelines page 35 (Click for TDS)
To obtain best efficency always use converter that uses most of the advised by producer current range. For MP432XX fammily there are following possibilites: MP4320 - 0.5A (Requires bigger coil L = 5.6uH, lower freq = 1.8Mhz) MP4321 - 1A (Requires bigger coil L = 5.6uH) MP4322 - 2A (current implemen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
(1206)
LAYOUT GUIDELINES:
NOTE:
OPT UVLO

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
